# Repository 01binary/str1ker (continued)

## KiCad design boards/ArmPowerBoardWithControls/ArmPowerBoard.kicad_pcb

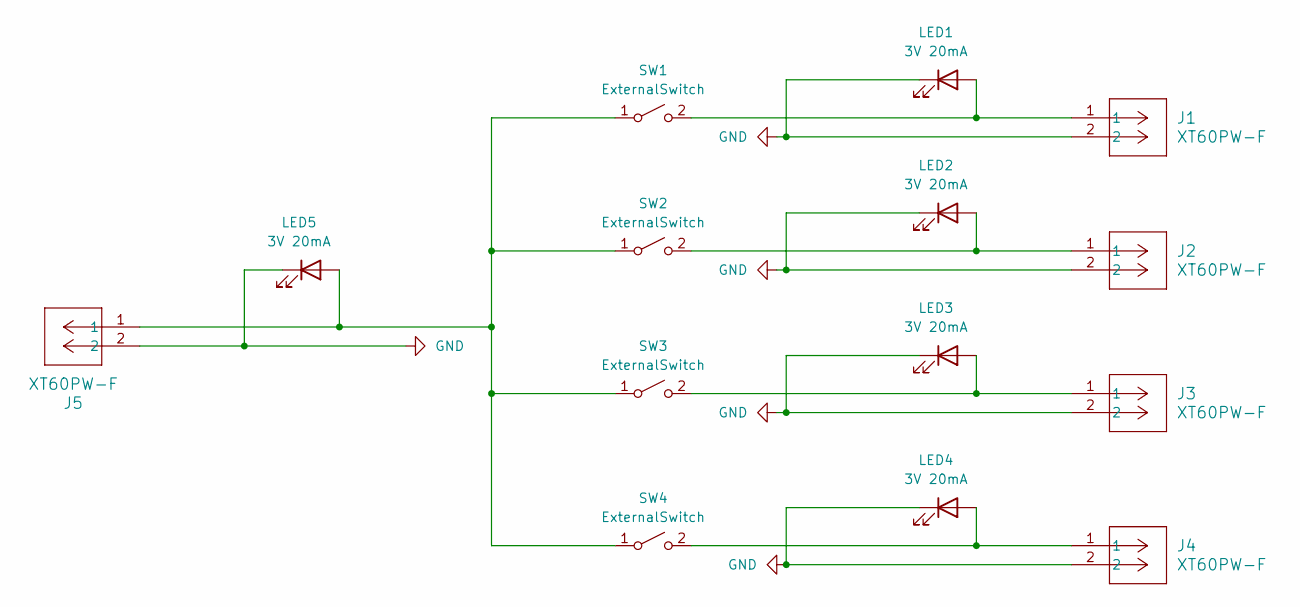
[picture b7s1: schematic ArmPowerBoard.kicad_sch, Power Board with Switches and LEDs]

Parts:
J1, J2, J3, J4, J5: XT60PW-F; XT-60-Measured
LED1, LED2, LED3, LED4, LED5: 3V 20mA; LED_D3.0mm
SW1, SW2, SW3, SW4: ExternalSwitch

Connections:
GND: J1.2, J2.2, J3.2, J4.2, J5.2, LED1.1 (K), LED2.1 (K), LED3.1 (K), LED4.1 (K), LED5.1 (K)
unnamed: J1.1, LED1.2 (A), SW1.2 (B)
unnamed: J2.1, LED2.2 (A), SW2.2 (B)
unnamed: J3.1, LED3.2 (A), SW3.2 (B)
unnamed: J4.1, LED4.2 (A), SW4.2 (B)
unnamed: J5.1, LED5.2 (A), SW1.1 (A), SW2.1 (A), SW3.1 (A), SW4.1 (A)

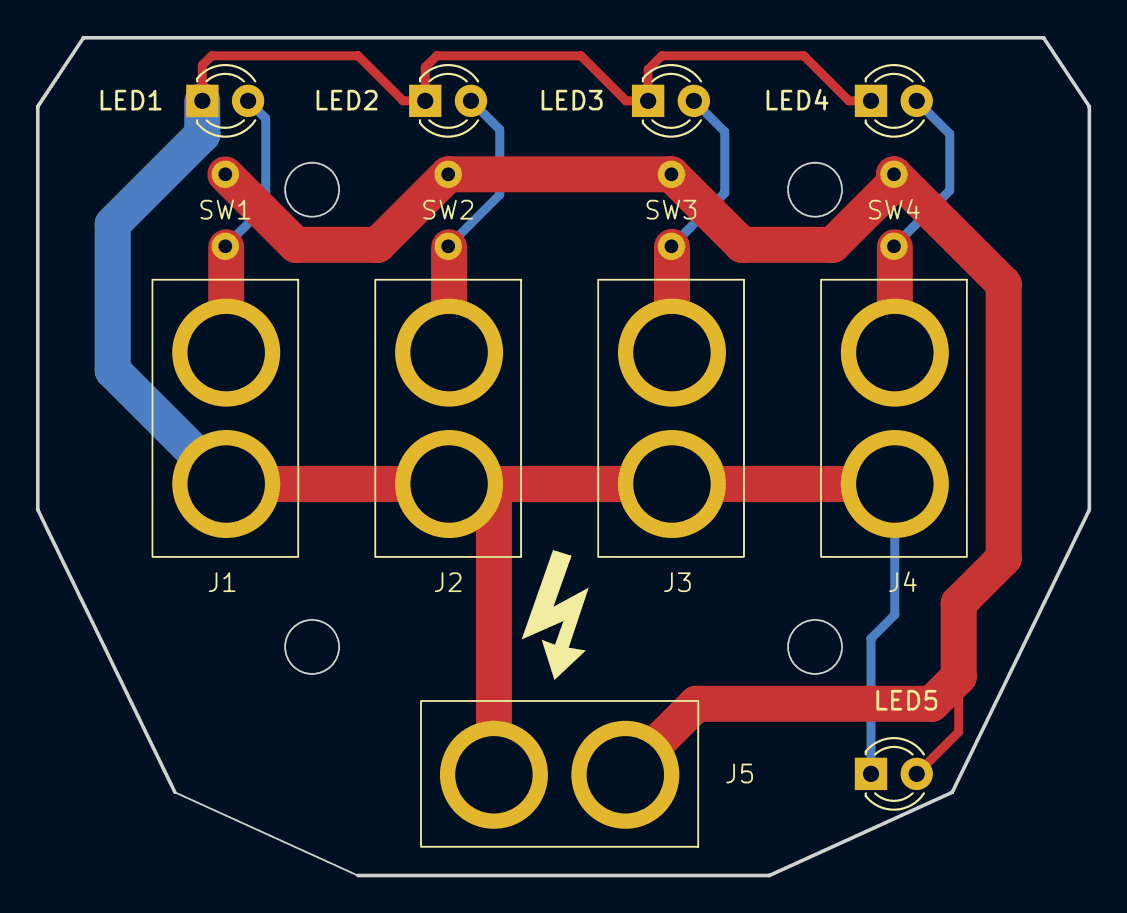
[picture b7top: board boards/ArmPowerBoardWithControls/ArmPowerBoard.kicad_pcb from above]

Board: 2 copper layers, 58.4 x 46.5 mm, 14 parts (0 on the bottom side), 6 nets.

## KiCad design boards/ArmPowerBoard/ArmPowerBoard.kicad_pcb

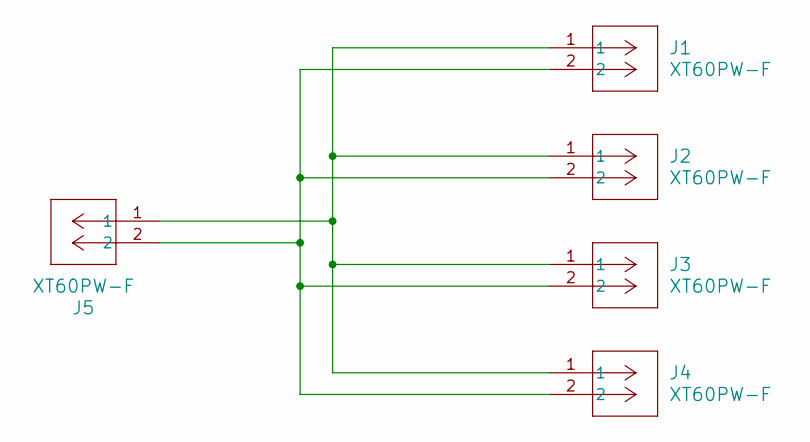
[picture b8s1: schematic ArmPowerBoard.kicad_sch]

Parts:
J1, J2, J3, J4, J5: XT60PW-F; XT-60-Measured

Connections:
unnamed: J1.1, J2.1, J3.1, J4.1, J5.1
unnamed: J1.2, J2.2, J3.2, J4.2, J5.2

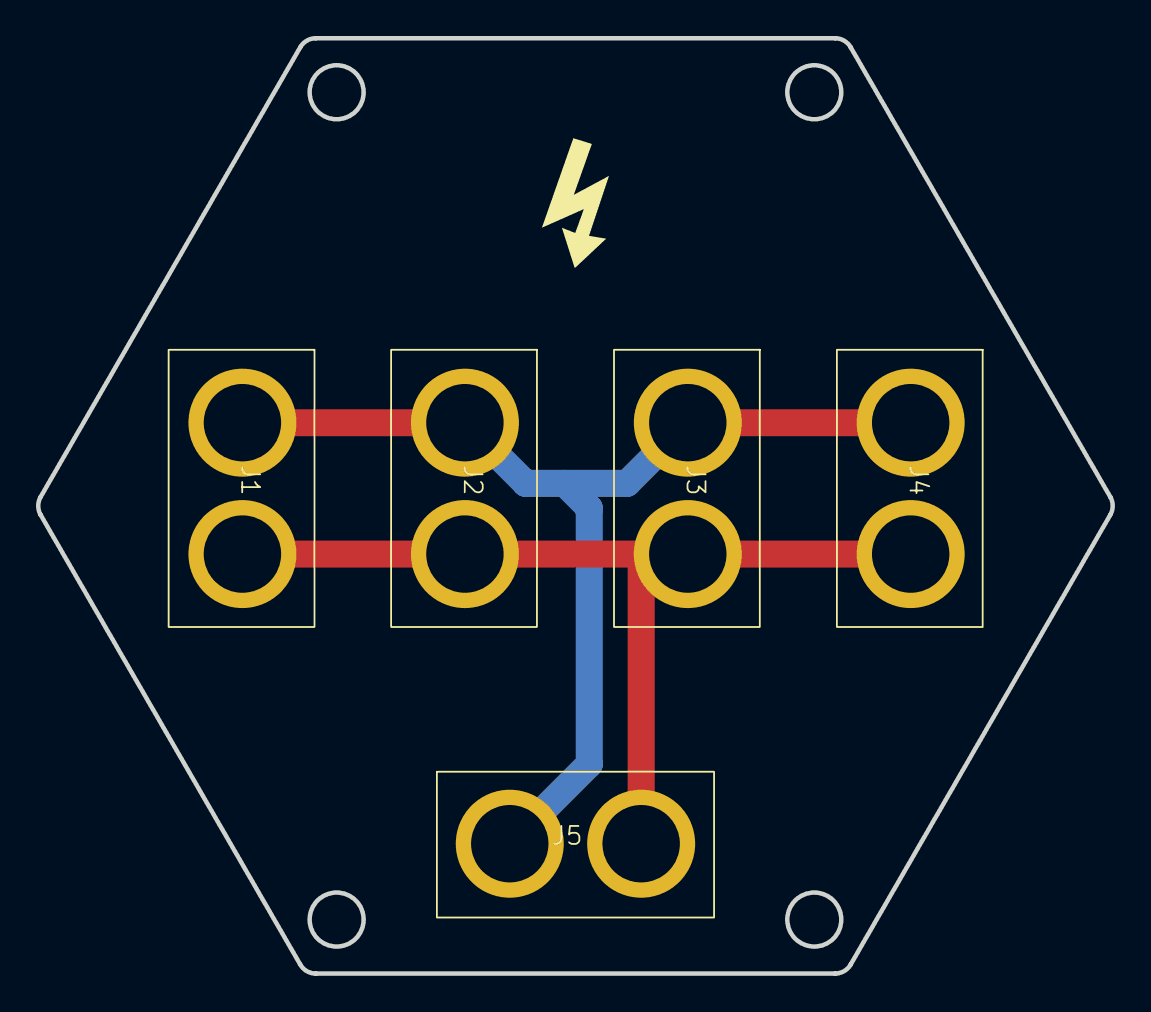
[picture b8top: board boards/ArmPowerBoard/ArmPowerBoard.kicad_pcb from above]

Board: 2 copper layers, 59.7 x 52.0 mm, 5 parts (0 on the bottom side), 2 nets.

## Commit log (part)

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2024-02-12 Remove old files
2024-02-12 Designing new chest controller
2024-02-12 Designing new chest
2024-03-15 New base with motor mount and encoder
2024-03-26 Merge
2024-03-26 Detail shoulder mount
2024-11-02 Reorganize project
2024-11-22 Freshen design concepts
2024-12-10 More work on head redo
2024-12-11 Try wendigo
2024-12-11 Blend with Kallamity
2025-01-20 Head and Arm design changes
2025-01-20 Fix compile errors switching from velocity to position control
2025-01-20 Update URDF after updating models
2025-01-20 Fix shoulder offset in URDF
2025-01-20 Nudge disconnected parts
2025-01-20 Fix shoulder offset after re-design
2025-01-21 Minor design updates
2025-01-24 Block out more methods
2025-01-25 Loading settings and state feedback instead of separate velocity and position
2025-01-25 Implement more methods
2025-01-25 Cleanup and tweaks
2025-01-29 Block out actuator and reorg
2025-01-30 Block out more final driver code
2025-01-30 No need for separate settings module
2025-01-30 More shortening
2025-01-30 Block out another driver
2025-01-31 Remove extra initialization complexity
2025-01-31 Cleanup
2025-01-31 Don't need SPI pins if running on Arduino
2025-01-31 Clean up ROS interface
2025-01-31 Comments no longer needed
2025-01-31 Missing constant
2025-02-02 Get hardware building again
2025-02-07 Fixing build errors
2025-02-07 All compile errors fixed
2025-02-08 Update designs
2025-02-08 Remove old designs and update chest
2025-02-08 Redo models
2025-02-09 Clean up, new body draft
2025-02-10 Neck external components
2025-02-10 Model new external parts
2025-02-11 Initial implementation of dynamic reconfigure
2025-02-11 Include the new header
2025-02-12 Get arm driver compiling without warnings
2025-02-12 Extra comment block
2025-02-12 First pass at reconfigure
2025-02-12 List of reconfigurable parameters
2025-02-13 Register settings for reconfigure server
2025-02-14 Registering settings goes along with EEPROM
2025-02-14 Advertise config on startup
2025-02-14 Include defaults when registering settings
2025-02-14 Initial implementation for describing parameters automatically
2025-02-14 Setup with Arduino Community
2025-02-16 New body preview
2025-02-16 Exports for CAD
2025-02-19 Update controllers
2025-02-19 Add power supply
2025-02-19 Add wireframe for spine link
2025-02-19 Update body design
2025-02-19 Body wireframe imported into inventor
2025-02-19 Redesign spine link
2025-02-19 New chest frame redesign
2025-02-26 Redo scapula sideways
2025-02-26 Arm scapula integration
2025-02-26 Chest integration
2025-03-01 Another iteration of chest design
2025-03-02 Chest frame re-design import
2025-03-02 Chest re-design source files
2025-03-02 Purge older files
2025-04-03 Stop using dynamic reconfigure and EEPROM, load settings using parameter server
2025-04-03 Separate launch file for hardware
2025-09-21 More re-designs and re-assembly
2025-09-21 Update design and doc
2025-09-21 Re-design lower body
2025-09-23 Torso encoder and alignment ring
2025-09-23 Front panel draft
2025-09-26 Front panel with instruments
2025-09-26 Initial torso lift connection
2025-09-27 Torso lift actuators mounting
2025-09-27 Preparing for spine re-design and connection to chest
2025-09-27 Re-developing pelvis and spine
2025-10-03 Spine detail
2025-10-03 More detailing on legs:
2025-10-06 Chest and legs detailing
2025-10-07 Detail MY6812 motor
2025-10-15 Legs finished
2025-10-20 Finalized legs and added handles
2025-10-21 Rename and resize leg parts for international shipping
2025-10-24 Leg handle and laser
2025-11-02 Begin placing electrical components
2025-11-04 More electrical components placed
2025-11-06 Place MeanWell power supply
2025-11-09 Arm fixture and new circuit breaker
2025-11-13 More cleanup and new electronics
2025-11-19 Mounting electric components in body
2025-12-04 More readme cleanup
2025-12-04 Add open boards
2025-12-06 Prepare for manufacturing
2025-12-10 Switch to using project library
2025-12-13 Address ERC and DRC violations
2025-12-13 Cleanup readme
2025-12-13 Re-generate manufacturing outputs
2025-12-17 Fixed LED footprint and re-exported
2026-01-08 Correct missing connections and two LED resistors because LEDs were too dim
2026-01-11 Add data sheets for two parts
2026-01-17 Design documents
2026-01-17 Minor edit
2026-01-17 Minor formatting
2026-01-17 Missed formatting
2026-01-17 Drop activity LED
2026-01-25 Initial board definition
2026-01-25 Get components
2026-01-25 Footprints for encoder board dependencies
2026-01-25 Head, body, legs work
2026-01-26 Redo neck and front with gearbox
2026-01-26 Leg actuators replaced with Antuator
2026-01-27 Install leg encoders
2026-01-29 Finalize legs and head
2026-01-29 Remove unused part
2026-01-29 Remove more unused parts
2026-01-29 Remove even more unused parts
2026-01-29 Remove two more unused parts
2026-01-29 Remove part used in old design
2026-01-29 Remove unused 4mm rod
2026-01-29 Remove 250mm shaft
2026-01-29 Remove another duplicate unused part
2026-01-29 Remove another duplicate and unused part
2026-01-29 Remove another duplicate or unused 120mm shaft
2026-01-31 Fix hi-z (floating) pins for solenoid and PWM channel 1
2026-01-31 Completed new arm board order
2026-02-01 Update doc for AS5045 board
2026-02-01 Normalize readmes
2026-02-01 Final normalize readme
2026-02-01 Pre-final leg encoder board
2026-02-03 Neck redesign pre-final
2026-02-04 Finalize head, leg actuators, laser
2026-02-09 Leg encoder board pre-final
2026-02-09 Plugin new wheel encoder footprint
2026-02-09 Fix typos
2026-02-09 Wrong schematic title
2026-02-09 Hopefully last typo
2026-02-09 Arm encoder initial bom update
2026-02-10 Pre-flight on two encoder boards
2026-02-11 Ordered leg encoder board
2026-02-11 Order arm encoder board, update bom
2026-02-11 Update documentation for two completed encoder boards
2026-02-12 Depth camera custom housing
2026-02-13 Debug Arduino serial not working
2026-02-13 More explicit load command
2026-02-13 Print loaded values
2026-02-13 Final board updates
2026-02-13 Minor readme edits
2026-02-13 Fixing config reading and dumping
2026-02-14 Fix loading settings on ROS Serial node
2026-02-14 Init leg board and update readme hero
2026-02-14 Clean up readme
2026-02-14 Dress up readme
2026-02-14 A bit more readme polish
2026-02-15 Draft position control
2026-02-15 Remove custom controller plugins
2026-02-15 Launch robot and hardware separately
2026-02-15 Fix PID control bugs
2026-02-15 Solenoid does not block
2026-02-15 Refactor for readability
2026-02-15 Styling changes
2026-02-15 A bit of cognitive load optimization
2026-02-17 Cleanup after AI
2026-02-17 Raw sensor message
2026-02-17 More launch separation
2026-02-17 Typo in settings
2026-02-18 Demo script
2026-02-18 Vision launch file
2026-02-21 Initial documentation update for leg robot board
2026-02-21 Arm workspace calculation
2026-02-21 Frame image
2026-02-22 Initial schematic
2026-02-24 Switch back to lamprey for neck
2026-02-25 Alignment flange for neck encoder PCB
2026-02-25 Add monolithic visor sub-parts
2026-03-03 Neck tilt potentiometer
2026-03-16 Arm demo
2026-03-17 Detail leg platform
2026-03-18 Cleanup and add features from pid tuner
2026-03-18 Details
2026-03-18 Fix compile error
2026-03-18 Finalize leg encoder board iteration
2026-03-20 Finalize and order leg board
2026-03-20 Readme updates for boards
2026-03-20 More cleanup on main board pinout
2026-03-21 Ordered lower body parts
2026-03-23 Detailing main board schematic
2026-03-24 Fix compile errors and make it work with Arduino in VSCode again
2026-03-24 Encoder data structure less fragile
2026-03-30 New configuration wip
2026-04-01 Update main and leg board
2026-04-02 Debug and re-design leg encoder and leg robot board
2026-04-06 Forearm config update
2026-04-06 Clamp potentiometer readings
2026-04-06 Initial leg driver sketch
2026-04-06 Fix compile errors
2026-04-07 Re-map pin assignments for leg board
2026-04-07 Another re-structure
2026-04-08 Minor normalization
2026-04-08 Minimal sketch for testing
2026-04-08 Test results
2026-04-10 Update leg encoder board and documentation
2026-04-10 Minor edits to leg encoder board readme
2026-04-10 Complete documentation for encoder boards
2026-04-10 Arm encoder code example
2026-04-10 Clean up leg robot board doc
2026-04-10 More leg board cleanup
2026-04-10 Normalize docs
2026-04-10 Typo and link
2026-04-10 Another typo and link
2026-04-10 More detail and cleanup for arm board
2026-04-10 Spacing
2026-04-10 More links
2026-04-14 Second iteration of leg robot board
2026-04-14 Order legs board
2026-04-18 Add OLED display, light bar, voltage and current sensors
2026-04-19 Re-routing main board, found a mistake
2026-04-19 Start audio board
2026-04-19 Start audio board schematic
2026-04-20 Schematic draft
2026-04-21 Cleanup and add main board firmware
2026-04-21 First draft of main board firmware
2026-04-21 Add battery meter
2026-04-21 Simplify setting status lights via shift register
2026-04-21 Clean up and refactor leg firmware
2026-04-21 Minor comment edits
2026-04-21 More cleanup in shift register
2026-04-21 Clean up constant names
2026-04-21 Clean up duplicated constant
2026-04-22 Update and cleanup comments
2026-04-22 Simplify comment
2026-04-22 More missing dependencies
2026-04-22 Fix compile errors on Teensy firmware
2026-04-22 Minor comment update
2026-04-22 Shorten comment
2026-04-22 Testing body firmware
2026-04-23 Finalize main board
2026-04-23 JLCPCB main board export for manufacturing
2026-04-24 Finalize mechanical design
2026-04-25 More board photographs
2026-04-25 Finalize audio board
2026-04-25 Seed audio board firmware
2026-04-26 Final export and order audio board
2026-04-26 Re-routing leg board after rotating IMU
2026-04-29 Add LED number displays to legs board and re-finalize
2026-04-30 Preflight leg robot board
2026-04-30 Main robot board preflight
2026-04-30 Initial voltage/current/power logic
2026-04-30 Clean up power display
2026-04-30 Fix bad temporary config
2026-04-30 Simplify teknic update
2026-05-04 Refactor metering
2026-05-04 Flatten file structure and add power controller
2026-05-04 Clean up
2026-05-05 Final board export after testing
2026-05-08 Pre-finalize mechanical
2026-05-11 Update audio firmware
2026-05-12 Finalize audio firmware
2026-05-12 Audio board debug todo
2026-05-13 Update power documentation again
2026-05-13 Re-finalize power documentation and schematic
2026-05-13 Minor wording
2026-05-13 Micro-edit
2026-05-15 Finalize electrical power design
2026-05-15 Re-route audio board
2026-05-17 Re-do back panel with bigger breaker
2026-05-20 Re-order leg board with different LED control chip
2026-05-20 Clean up and re-modeling battery based on 3D scan
2026-05-26 Place battery from 3D scan
2026-05-26 Contactor mount on bottom panel
2026-05-27 Finalize power diagram and draft back panel silk screen
2026-05-27 Main board encoder documentation
2026-05-28 Finalize body panels
2026-05-29 Leg board re-do LED displays, main board prepare for re-routing
2026-05-29 Re-route main board after flipping battery meter and removing INA260
2026-05-31 Testing main board
2026-05-31 Update leg board documentation
2026-05-31 Test wheel board
2026-05-31 Minor doc updates
2026-05-31 Ignore KiCad history
2026-06-02 Another iteration of boards
2026-06-06 XT60E-F connector for power distribution blocks
2026-06-06 Finalze and cut depth camera housing
2026-06-06 Add battery mounts from Amazon
2026-06-06 Illuminated switch
2026-06-07 12-port power hub
2026-06-09 Power hub re-design
2026-06-13 Leg board retest
2026-06-13 Re-do breaker mount with power hub and new AC receptacle
2026-06-16 Re-designing main board
2026-06-17 Finalize main board re-design pin assignments
2026-06-18 Level shifting on main robot board
2026-06-20 Pre-flight main board
2026-06-22 New leg board documentatione
2026-06-22 Re-finalize leg board
2026-06-23 Working number display test
2026-06-23 Calibrating voltage divider
2026-06-23 Ignore KiCad files
2026-06-23 Clean up KiCad files
2026-06-23 Add KiCad info cache to git ignore
2026-06-25 Non-conductive power routing board back
2026-06-25 Final encoder spacer
2026-06-25 Frame screen mount
2026-06-25 Unused parts
2026-06-25 Integrate new arm power board lid
2026-06-27 Finalize touch screen hood
2026-06-27 Battery safety caps
